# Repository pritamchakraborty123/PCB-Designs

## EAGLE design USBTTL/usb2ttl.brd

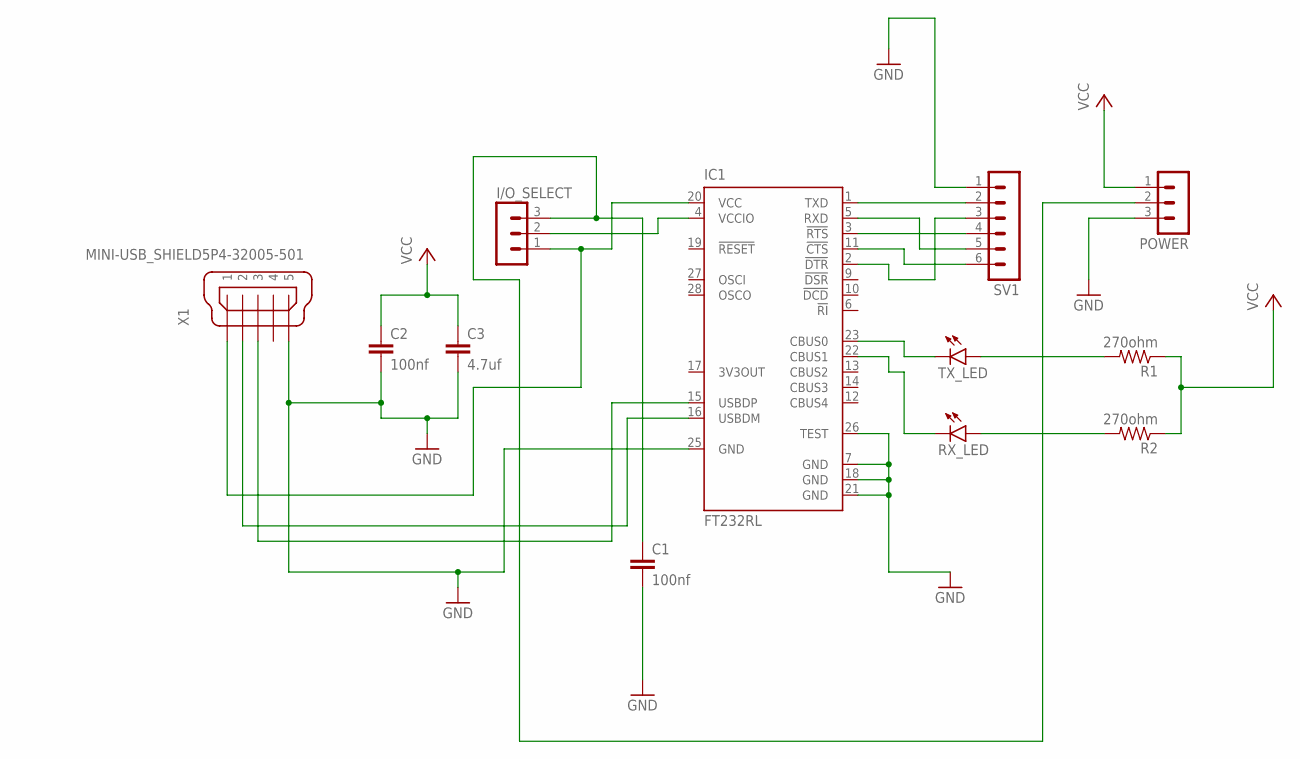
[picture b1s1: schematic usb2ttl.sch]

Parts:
C1, C2: 100nf; C2.5-3
C3: 4.7uf; C2.5-3
I/O_SELECT: MA03-1
IC1: FT232RL; SSOP28
POWER: MA03-1
R1, R2: 270ohm; 0204/7
RX_LED: LED5MM
SV1: MA06-1
TX_LED: LED5MM
X1: MINI-USB_SHIELD5P4-32005-501; 32005-501

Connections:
GND: C1.2, C2.2, C3.2, IC1.7 (GND), IC1.18 (GND), IC1.21 (GND), IC1.25 (GND), IC1.26 (TEST), POWER.3, SV1.1, X1.5
unnamed: I/O_SELECT.1, IC1.20 (VCC), X1.1
unnamed: I/O_SELECT.2, IC1.4 (VCCIO)
unnamed: C1.1, I/O_SELECT.3, POWER.2
unnamed: IC1.15 (USBDP), X1.3
unnamed: IC1.16 (USBDM), X1.2
unnamed: IC1.1 (TXD), SV1.2
unnamed: IC1.5 (RXD), SV1.5
unnamed: IC1.3 (!RTS), SV1.4
unnamed: IC1.11 (!CTS), SV1.6
unnamed: IC1.2 (!DTR), SV1.3
unnamed: IC1.23 (CBUS0), TX_LED.K (C)
unnamed: IC1.22 (CBUS1), RX_LED.K (C)
unnamed: R1.2, TX_LED.A
unnamed: R2.2, RX_LED.A
VCC: C2.1, C3.1, POWER.1, R1.1, R2.1

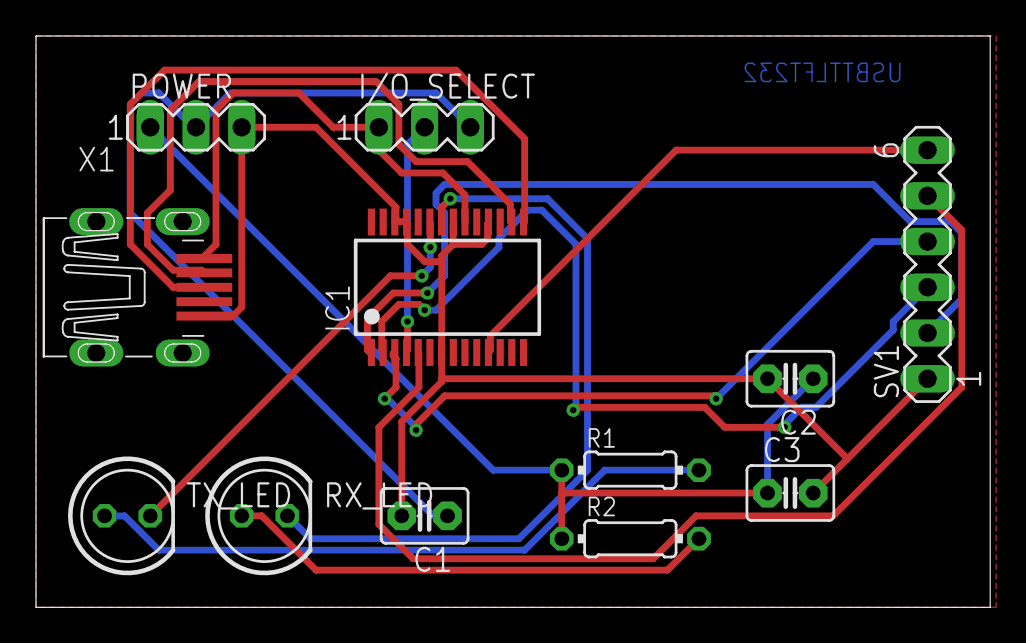
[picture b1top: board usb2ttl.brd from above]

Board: 2 copper layers, 53.0 x 31.7 mm, 12 parts (0 on the bottom side), 16 nets.

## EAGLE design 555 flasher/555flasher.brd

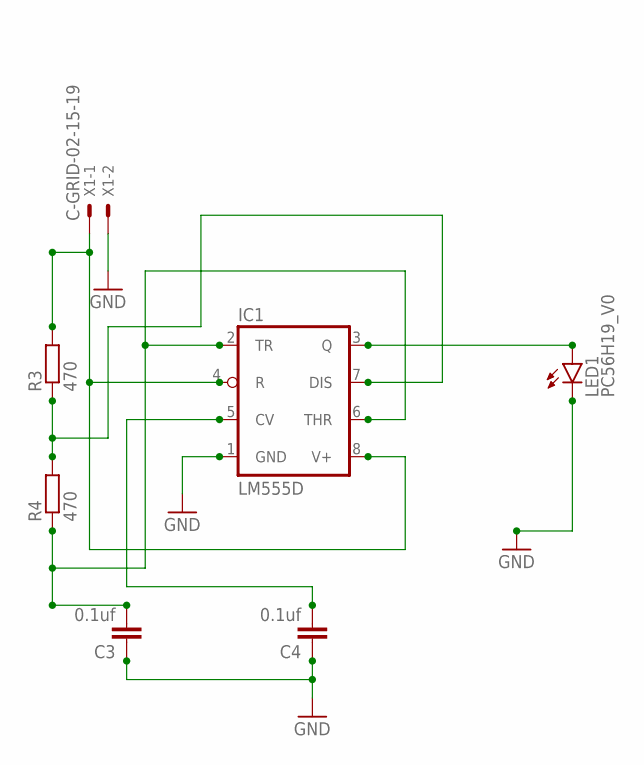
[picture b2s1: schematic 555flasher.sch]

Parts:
C3, C4: 0.1uf; C0805
IC1: LM555D; SO08
LED1: PC56H19_V0
R3, R4: 470; R0805
X1: C-GRID-02-15-19; 15-91-02

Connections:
GND: C3.1, C4.1, IC1.1 (GND), LED1.1 (C), LED1.3 (C), X1.2
unnamed: IC1.4 (R), IC1.8 (V+), R3.2, X1.1
unnamed: C4.2, IC1.5 (CV)
unnamed: IC1.7 (DIS), R3.1, R4.2
unnamed: C3.2, IC1.2 (TR), IC1.6 (THR), R4.1
unnamed: IC1.3 (Q), LED1.2 (A), LED1.4 (A)

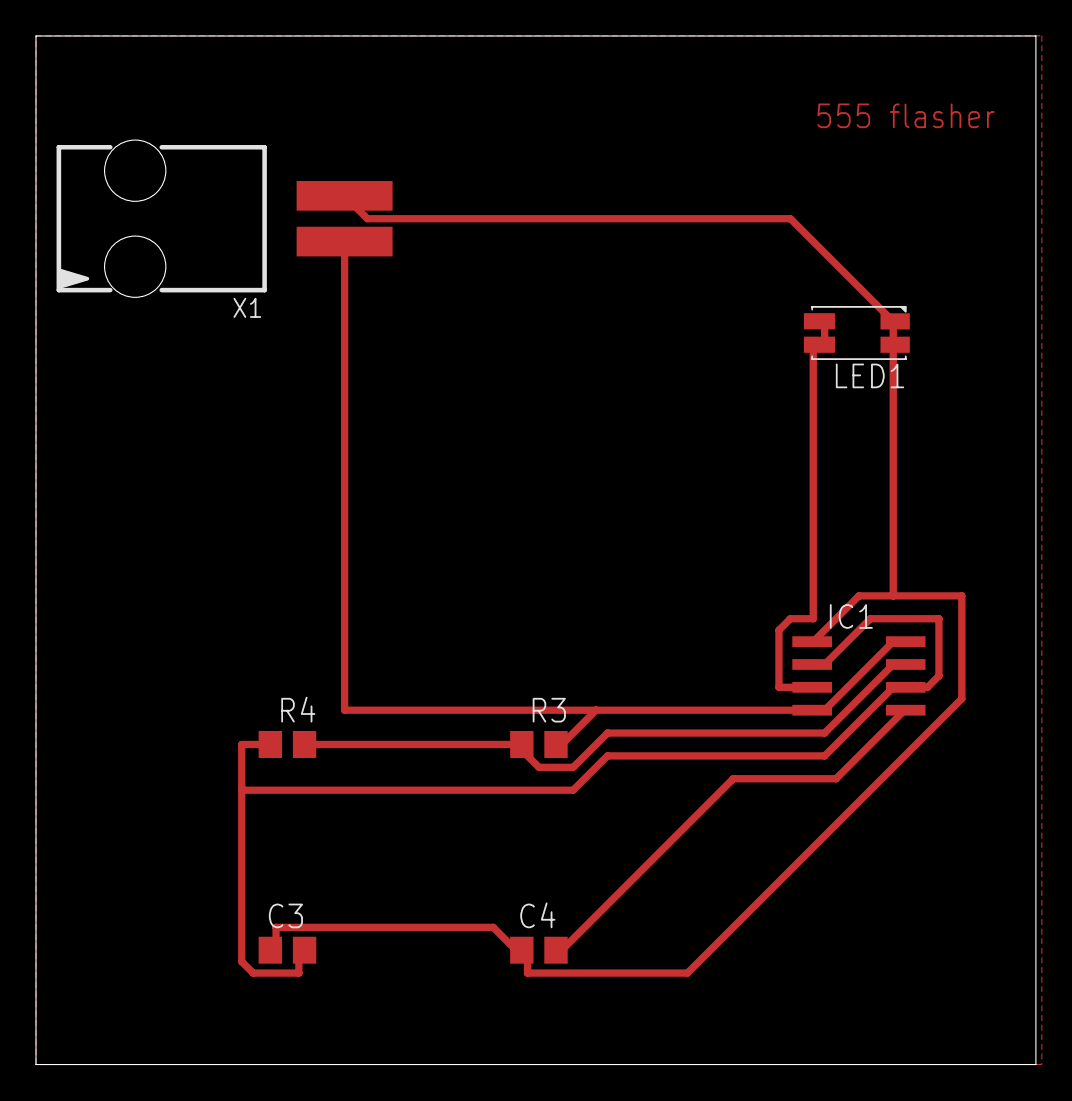
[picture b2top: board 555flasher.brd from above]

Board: 2 copper layers, 55.5 x 57.1 mm, 7 parts (0 on the bottom side), 6 nets.

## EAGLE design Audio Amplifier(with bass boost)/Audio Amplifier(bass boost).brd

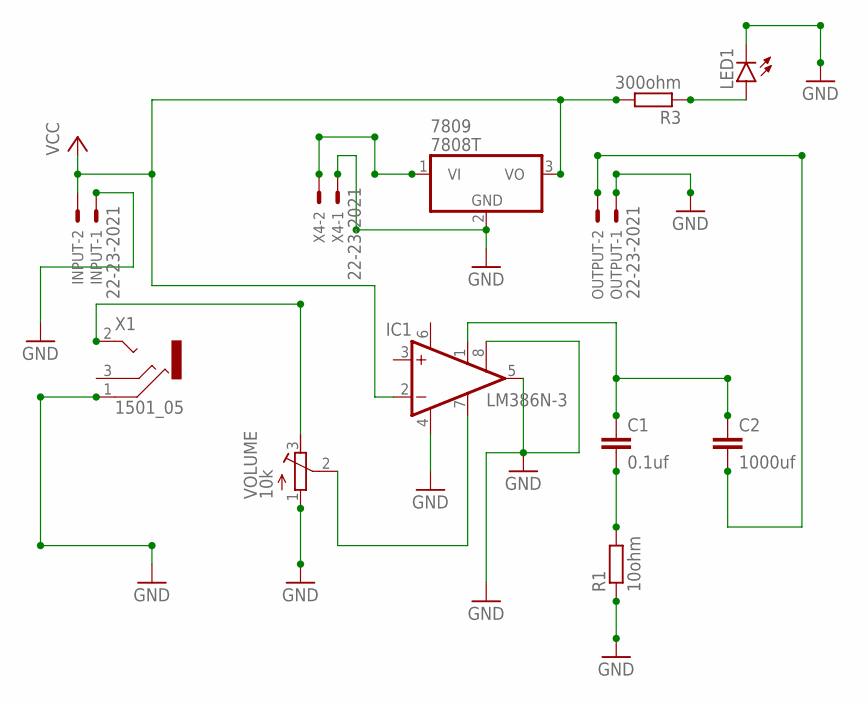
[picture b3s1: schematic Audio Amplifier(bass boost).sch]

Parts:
7809: 7808T; TO220H
C1: 0.1uf; C2.5-2
C2: 1000uf; C5B3
IC1: LM386N-3; DIL08
INPUT: 22-23-2021
LED1: LED5MM
OUTPUT: 22-23-2021
R1: 10ohm; 0207/7
R3: 300ohm; 0207/7
VOLUME: 10k; RTRIM64W
X1: 1501_05
X4: 22-23-2021

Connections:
GND: 7809.2 (GND), IC1.4 (GND), IC1.5 (OUT), IC1.8 (GAIN), INPUT.1, LED1.K (C), OUTPUT.1, R1.1, VOLUME.1 (A), X1.1, X4.1
unnamed: VOLUME.3 (E), X1.2
unnamed: IC1.7 (BYPASS), VOLUME.2 (S)
unnamed: C1.1, C2.1, IC1.1 (GAIN)
unnamed: C1.2, R1.2
unnamed: C2.2, OUTPUT.2
unnamed: 7809.1 (VI), X4.2
unnamed: LED1.A, R3.1
VCC: 7809.3 (VO), IC1.2 (-IN), INPUT.2, R3.2
VS: IC1.6 (VS)

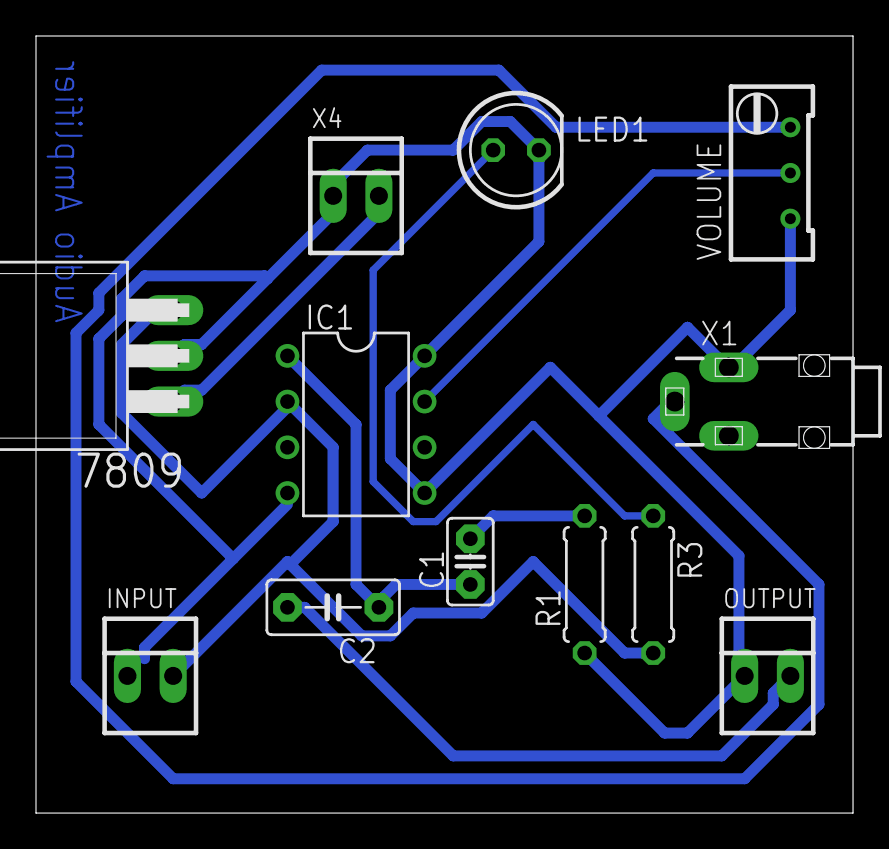
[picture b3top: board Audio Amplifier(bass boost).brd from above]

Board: 2 copper layers, 45.4 x 43.2 mm, 12 parts (0 on the bottom side), 9 nets.

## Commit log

2020-06-05 Added PCB designs
